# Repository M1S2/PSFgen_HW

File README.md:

# PS_Fgen_HW
Hardware for an PowerSupply and Functiongenerator build from an ATX power supply.

## ATX Supply
The hardware of the power supply and function generator is based on the following ATX supply:
``Yuan Kee 230P ATX``

By using another ATX supply, some output capabilities can be changed / enhanced.

## Input / Output Capabilities

The power supply and function generator features the following capabilites:

### Power Supply output (PS+)
One power supply output is available.
Connector		| PS+
-----------------------	| -----------------
Voltage			| 0 .. 10 V DC
Current			| 0 .. 2 A
Protections		| OVP, OCP, OPP

The voltage and current regulation is done in firmware.
The protections are implemented in firmware, too.

### DDS outputs (DDS1, DDS2)
Two direct digital synthesis outputs are available.
Connector		| DDS1						| DDS2
-----------------------	| ---------------------------------------------	| ---------------------------------------------
Amplitude		| 0 .. 20 Vpp					| 0 .. 20 Vpp
Offset			| -10 V .. 10 V					| -10 V .. 10 V
Frequency		| approx. max. 170 kHz				| approx. max. 170 kHz
Waveforms		| FW defined (Sine, Square, Triangle, ...)	| FW defined (Sine, Square, Triangle, ...)

The waveforms are defined in firmware. Default waveforms like sine, square and triangle are supported. By using DDS it is possible to even generate user defined waveforms.
The maximum frequency is limited by the low pass filter after the DAC outputs. The cutoff frequency is approximately 170 kHz. The real frequency range depends on the DDS implementation in the firmware!

### DMM inputs (DMM1, DMM2)
Two digital multimeter inputs are available.
Connector	| DMM1		| DMM2
---------------	| -------------	| ---------------
Input Range	| 0 .. 20 V DC	| 0 .. 20 V DC

Negative voltages on the DMM inputs between -20 V and 0 V are allowed but the output is clipped to 0 V!
The measured voltage for negative inputs is 0 V and a warning signal is generated.

### USB outputs
Two USB outputs are available. They are connected to the 5V output of the ATX supply. So the combined current capability for both USB ports are 23 A.

### USB input
The USB input can be used to communicate to the device via serial port.

### ATX outputs
All output voltages of the ATX supply are directly available through connectors on the connector panel. The currents are directly depending on the used ATX supply (values for the Yuan Kee 230P ATX).
Connector		| +5V	| +3V3	| +12V	| -12V
-----------------------	| -----	| -----	| -----	| -----
Voltage			| 5 V	| 3,3 V	| 12 V	| -12 V
Current (max.)		| 23 A	| 14 A	| 9 A	| 0.8 A

## User Interface

The user interface is made up of the following components:
- Graphical display: A 320x240 pixel graphical LCD is used to display the device status and current settings.
- Encoder: A rotary encoder can be used for value editing and menu navigation.
- KeyPad: A 16 button keypad can be used for value editing and menu navigation.
- OnOffControls: A PCB with buttons and LEDs for faster enabling of the channels and status display.

The user interface logic is defined by the firmware.

## Electronic
The electronic is divided into the following PCBs:
- **FrontPanel:** The front panel is containing 16 push buttons forming a 4x4 keypad and a rotary encoder for user input. It is connected to the MainBoard using a ribbon cable.
- **MainBoard:** The main board is containing all other components that can be grouped like following:
	- *Microcontroller*: The main controller of the power supply and function generator. It controls everything from user input handling to output generation. The used type is an ATmega1284P.
	- *Serial communication:* A FT232RL USB-UART IC is used for serial communication to the microcontroller via USB.
	- *GLCD:* The used graphic LCD model is ``ILI9341``. It has 320x240 pixels and is controllable via SPI. **Important:** The display uses a 3.3 V logic level!
	- *ATX voltage monitors:* The ATX 5 V and 3.3 V lines are each directly connected to ADCs of the microcontroller. The 12V and -12V lines aren't monitored anymore because the input pins were needed for other purposes.
	- *DMM inputs:* The two DMM inputs can be used to measure positive input voltages. The resistor divider scales the input voltage so that the maximum DMM input voltage equals 5 V (maximum allowed voltage of the microcontroller ADC inputs).  **Important:** Voltages higher than the maximum DMM input voltage can damage the inputs.
	- *DDS outputs:* The two DDS output signals are generated by a dual output DAC IC (MCP4921, output 0..5 V for each output) followed by an offset and amplification stage (used to create a range of -10 V .. 10 V). The output is buffered by an OpAmp and two transistors for higher currents.
	- *PS output:* The PS output signal is generated by a single output DAC IC (MCP4921, output 0..5 V) and buffered by an OpAmp and two transistors for higher currents. The voltage at the PS output is measured by a simple resistor voltage divider. The current at the PS output is measured by transforming it into a voltage proportional to the current.
- **DMMRectifier:** The DMMRectifier is used to protect the ADC DMM inputs from negative inputs on the DMM1 and DMM2 connectors. Negative voltages are clipped to 0 V and a warning signal is generated when the voltage on the inputs are negative.
- **OnOffControls:** The OnOffControls are buttons and LEDs for faster enabling of the channels and status display.

The FrontPanel, DMMRectifier and OnOffControls PCBs were designed to be manufactured with toner transfer method.

The MainBoard PCB was too complex for manual manufacturing and was therefore made by JLCPCB.

!!! :warning: Caution: The MainBoard was designed to a size of 100 x 100 mm to fit the maximum size of JLCPCB. Eagle changed the maximum board size to 100 x 80 mm in 2022. Therefore the board can't be modified anymore. But the schematics are up-to-date. !!! 

## Housing
All housing components are made for the above ATX supply and are not guaranteed to fit for any other ATX supply. Nevertheless all construction files are available in the Mechanical folder and can be adapted, if neccessary.
The parts were designed using Autodesk Fusion 360 (.f3d files) and are exported as .stl files.
The .stl files were used to 3D print all components.
All parts are needed once, except the `Standfuss.stl` (needed 4x).

## Firmware
The firmware for this power supply and function generator is developed in another repository:
[GitHub - M1S2/PS_Fgen_FW: Firmware for an Power Supply and Function Generator build from an ATX power supply](https://github.com/M1S2/PS_Fgen_FW)

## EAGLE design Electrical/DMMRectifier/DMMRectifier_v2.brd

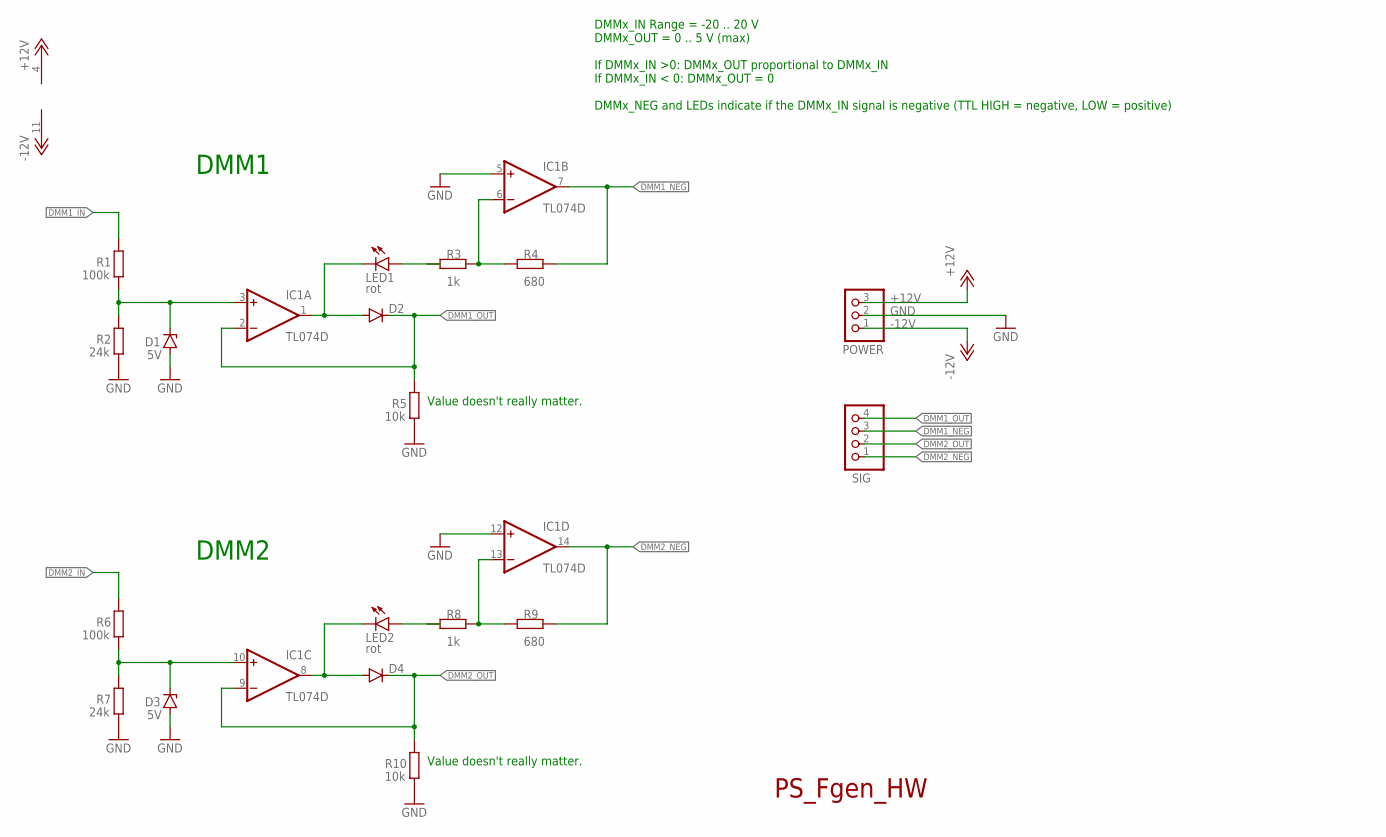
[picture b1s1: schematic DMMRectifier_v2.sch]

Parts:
D1, D3: 5V; SOD80C
D2, D4: DIODE-SOD80C; SOD80C
IC1: TL074D; SO14
LED1, LED2: rot; CHIPLED_0603
POWER: PINHD-1X3; 1X03
R1, R6: 100k; R0805
R2, R7: 24k; R0805
R3, R8: 1k; R0805
R4, R9: 680; R0805
R5, R10: 10k; R0805
SIG: PINHD-1X4; 1X04

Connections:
+12V: IC1.4 (V+), POWER.3
-12V: IC1.11 (V-), POWER.1
DMM1_IN: R1.2
DMM1_NEG: IC1.7 (OUT), R4.1, SIG.3
DMM1_OUT: D2.C, IC1.2 (-IN), R5.2, SIG.4
DMM2_IN: R6.2
DMM2_NEG: IC1.14 (OUT), R9.1, SIG.1
DMM2_OUT: D4.C, IC1.9 (-IN), R10.2, SIG.2
GND: D1.A, D3.A, IC1.5 (+IN), IC1.12 (+IN), POWER.2, R2.1, R5.1, R7.1, R10.1
unnamed: D1.C, IC1.3 (+IN), R1.1, R2.2
unnamed: D3.C, IC1.10 (+IN), R6.1, R7.2
unnamed: IC1.6 (-IN), R3.1, R4.2
unnamed: D2.A, IC1.1 (OUT), LED1.C
unnamed: LED1.A, R3.2
unnamed: IC1.13 (-IN), R8.1, R9.2
unnamed: D4.A, IC1.8 (OUT), LED2.C
unnamed: LED2.A, R8.2

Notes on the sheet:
PS_Fgen_HW
DMMx_IN Range = -20 .. 20 V DMMx_OUT = 0 .. 5 V (max) If DMMx_IN >0: DMMx_OUT proportional to DMMx_IN If DMMx_IN < 0: DMMx_OUT = 0 DMMx_NEG and LEDs indicate if the DMMx_IN signal is negative (TTL HIGH = negative, LOW = positive)
DMM1
DMM2
Value doesn't really matter.

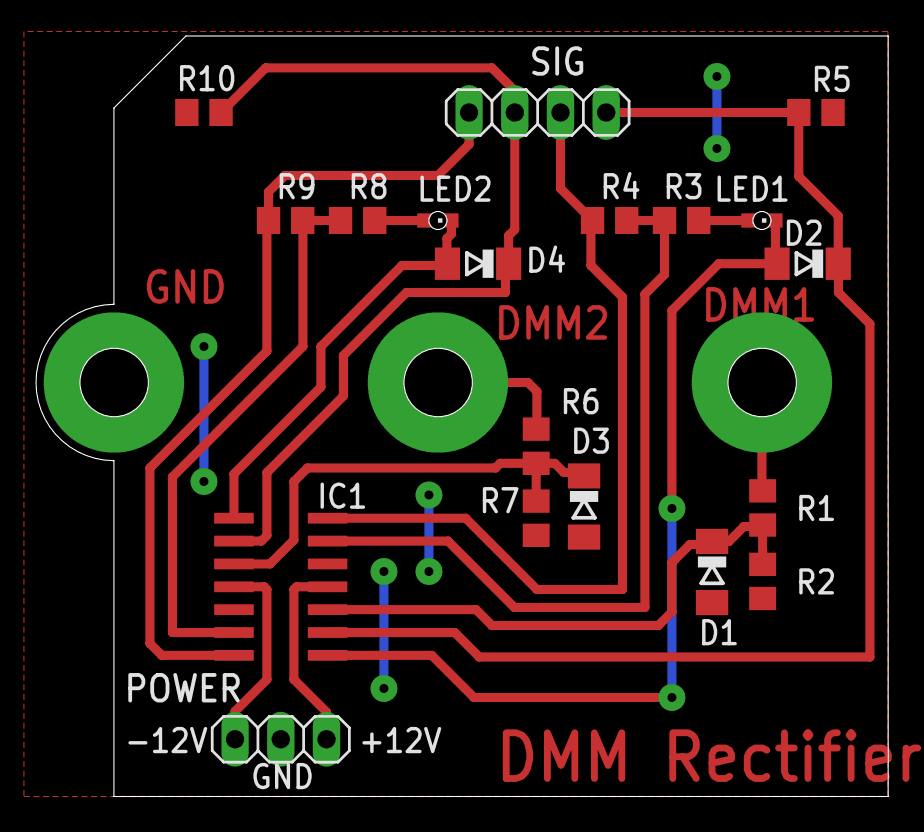
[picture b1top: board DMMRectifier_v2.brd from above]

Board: 2 copper layers, 47.3 x 42.2 mm, 19 parts (0 on the bottom side), 15 nets.

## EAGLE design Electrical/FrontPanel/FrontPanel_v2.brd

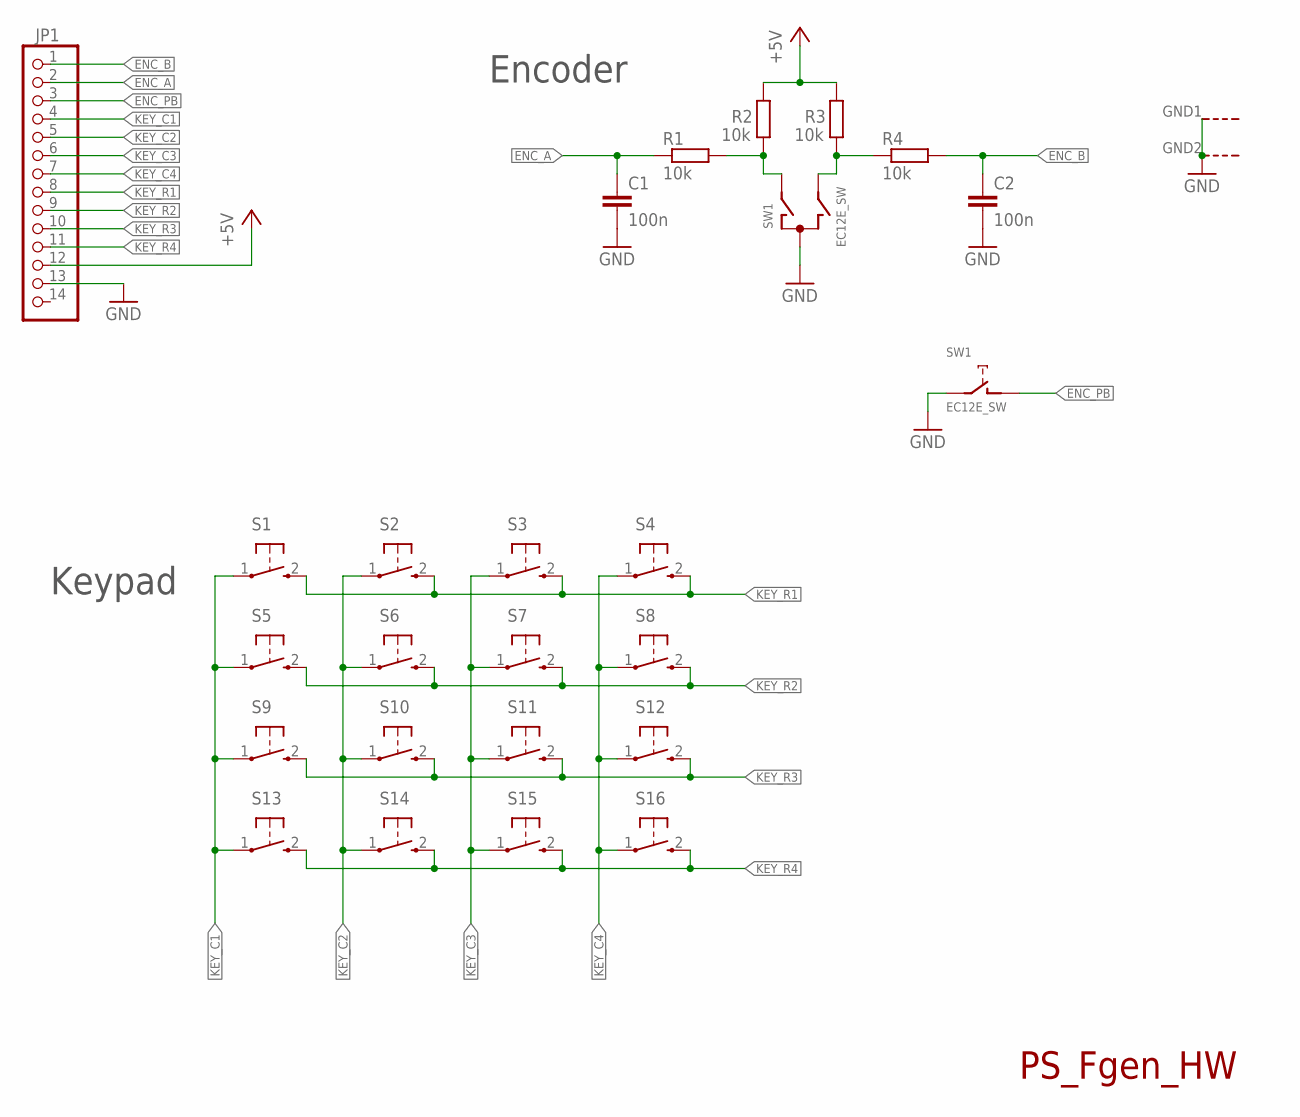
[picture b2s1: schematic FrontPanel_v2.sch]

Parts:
C1, C2: 100n; C0805
JP1: PINHD-1X14; 1X14
R1, R2, R3, R4: 10k; R0805
S1, S2, S3, S4, S5, S6, S7, S8, S9, S10, S11, S12, S13, S14, S15, S16: KURZHUBTASTER; B3F-10XX
SW1: EC12E_SW; ALPS_EC12E_SW

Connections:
+5V: JP1.12, R2.2, R3.2
ENC_A: C1.1, JP1.2, R1.1
ENC_B: C2.1, JP1.1, R4.2
ENC_PB: JP1.3, SW1.D (1)
GND: C1.2, C2.2, JP1.13, SW1.C, SW1.E (2), SW1.GND1 (G), SW1.GND2 (G)
KEY_C1: JP1.4, S1.1, S5.1, S9.1, S13.1
KEY_C2: JP1.5, S2.1, S6.1, S10.1, S14.1
KEY_C3: JP1.6, S3.1, S7.1, S11.1, S15.1
KEY_C4: JP1.7, S4.1, S8.1, S12.1, S16.1
KEY_R1: JP1.8, S1.2 (S), S2.2 (S), S3.2 (S), S4.2 (S)
KEY_R2: JP1.9, S5.2 (S), S6.2 (S), S7.2 (S), S8.2 (S)
KEY_R3: JP1.10, S9.2 (S), S10.2 (S), S11.2 (S), S12.2 (S)
KEY_R4: JP1.11, S13.2 (S), S14.2 (S), S15.2 (S), S16.2 (S)
unnamed: R1.2, R2.1, SW1.A
unnamed: R3.1, R4.1, SW1.B

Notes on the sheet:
PS_Fgen_HW
Keypad
Encoder

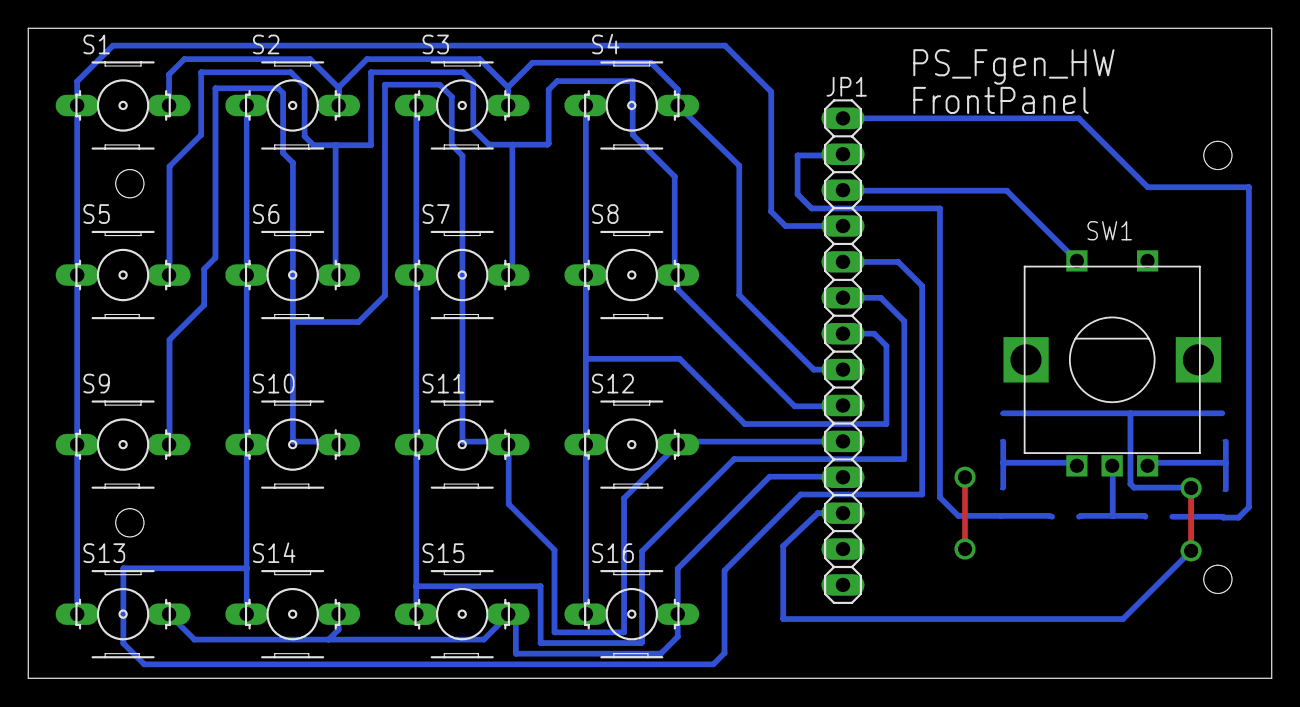
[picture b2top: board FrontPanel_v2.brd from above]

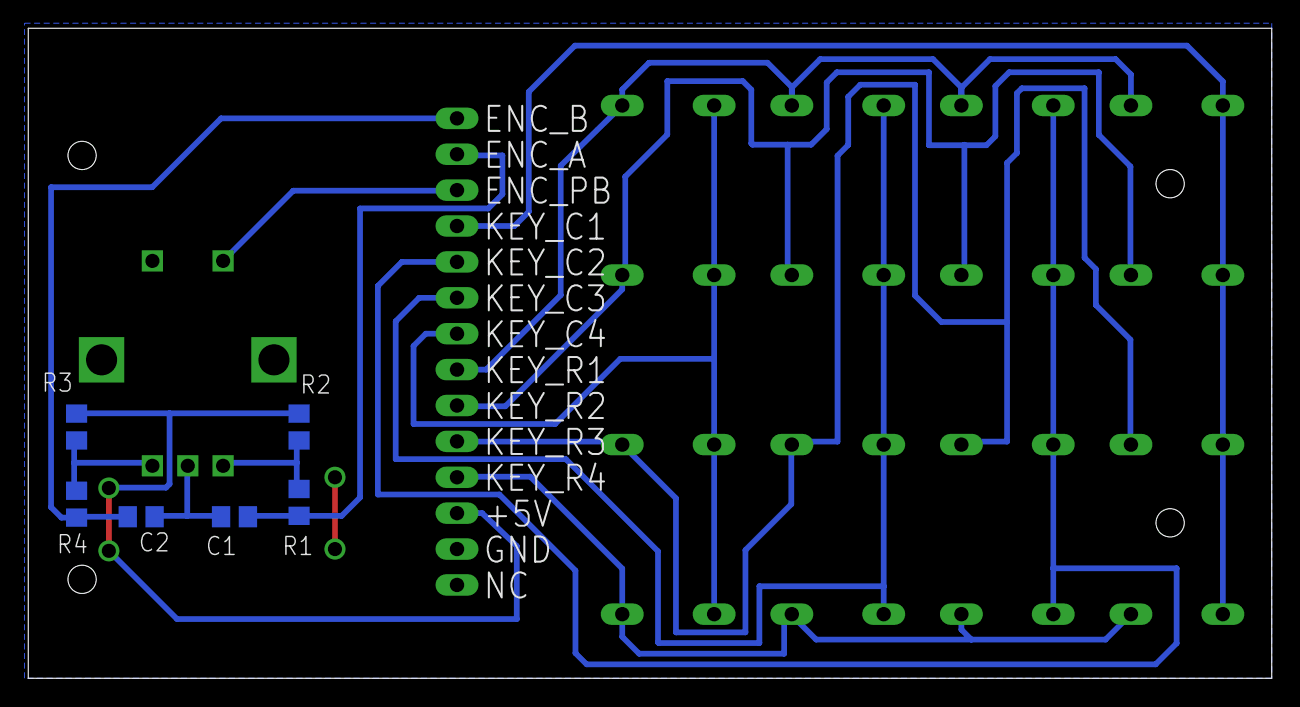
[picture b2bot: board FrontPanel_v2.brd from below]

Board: 2 copper layers, 88.0 x 46.0 mm, 24 parts (6 on the bottom side), 15 nets.

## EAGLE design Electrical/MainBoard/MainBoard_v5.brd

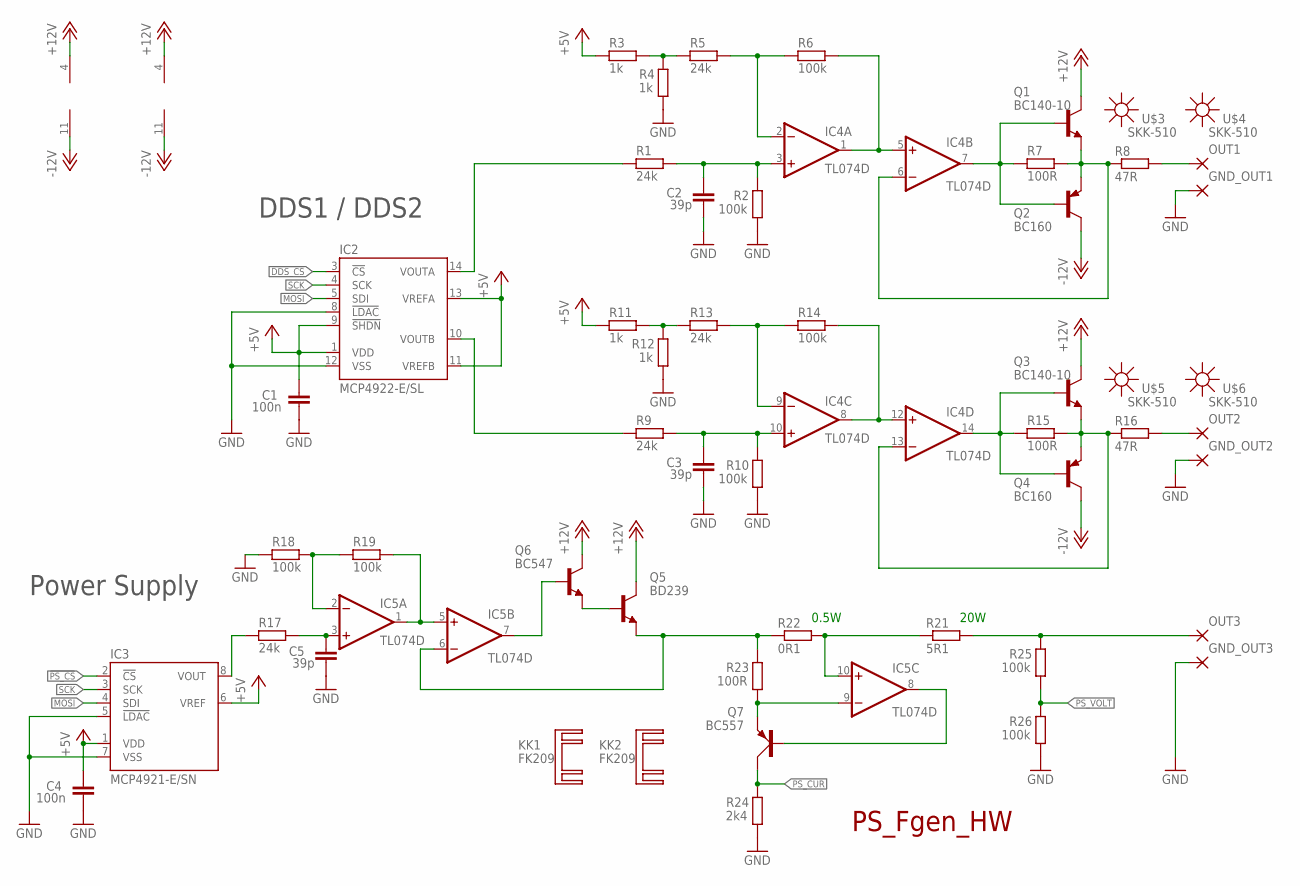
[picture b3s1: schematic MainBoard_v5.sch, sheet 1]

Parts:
C1, C4: 100n; C0805
C2, C3, C5: 39p; C0805
GND_OUT1, GND_OUT2, GND_OUT3: 2,54/1,0
IC2: MCP4922-E/SL; SO14
IC3: MCP4921-E/SN; SO08
IC4, IC5: TL074D; SO14
KK1, KK2: FK209
OUT1, OUT2, OUT3: 2,54/1,0
Q1, Q3: BC140-10; TO39
Q2, Q4: BC160; TO39
Q5: BD239; CB-274
Q6: BC547; TO92
Q7: BC557; SOT54A
R1, R5, R9, R13, R17: 24k; R0805
R2, R6, R10, R14, R18, R19, R25, R26: 100k; R0805
R3, R4, R11, R12: 1k; R0805
R7, R15, R23: 100R; R0805
R8, R16: 47R; 0411/15
R21: 5R1; 0411/15
R22: 0R1; 0411/15
R24: 2k4; R0805
U$3, U$4, U$5, U$6: SKK-510; SKK

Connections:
!DDS_CS: IC2.3 (!CS); also elsewhere on the board
!PS_CS: IC3.2 (!CS); also elsewhere on the board
+5V: C1.2, C4.2, IC2.1 (VDD), IC2.9 (!SHDN), IC2.11 (VREFB), IC2.13 (VREFA), IC3.1 (VDD), IC3.6 (VREF), R3.1, R11.1; also elsewhere on the board
+12V: IC4.4 (V+), IC5.4 (V+), Q1.3 (C), Q3.3 (C), Q5.T2 (C), Q6.3 (C); also elsewhere on the board
-12V: IC4.11 (V-), IC5.11 (V-), Q2.3 (C), Q4.3 (C); also elsewhere on the board
GND: C1.1, C2.1, C3.1, C4.1, C5.1, GND_OUT1.1, GND_OUT2.1, GND_OUT3.1, IC2.8 (!LDAC), IC2.12 (VSS), IC3.5 (!LDAC), IC3.7 (VSS), R2.1, R4.1, R10.1, R12.1, R18.1, R24.1, R26.1; also elsewhere on the board
MOSI: IC2.5 (SDI), IC3.4 (SDI); also elsewhere on the board
unnamed: IC2.14 (VOUTA), R1.1
unnamed: C2.2, IC4.3 (+IN), R1.2, R2.2
unnamed: R3.2, R4.2, R5.1
unnamed: IC4.2 (-IN), R5.2, R6.1
unnamed: IC4.7 (OUT), Q1.2 (B), Q2.2 (B), R7.1
unnamed: IC4.1 (OUT), IC4.5 (+IN), R6.2
unnamed: IC4.6 (-IN), Q1.1 (E), Q2.1 (E), R7.2, R8.1
unnamed: R11.2, R12.2, R13.1
unnamed: IC4.9 (-IN), R13.2, R14.1
unnamed: C3.2, IC4.10 (+IN), R9.2, R10.2
unnamed: IC4.8 (OUT), IC4.12 (+IN), R14.2
unnamed: IC2.10 (VOUTB), R9.1
unnamed: IC4.14 (OUT), Q3.2 (B), Q4.2 (B), R15.1
unnamed: IC4.13 (-IN), Q3.1 (E), Q4.1 (E), R15.2, R16.1
unnamed: IC3.8 (VOUT), R17.1
unnamed: C5.2, IC5.3 (+IN), R17.2
unnamed: IC5.2 (-IN), R18.2, R19.1
unnamed: IC5.6 (-IN), Q5.G (E), R22.1, R23.2
unnamed: IC5.1 (OUT), IC5.5 (+IN), R19.2
unnamed: Q5.T1 (B), Q6.1 (E)
unnamed: OUT3.1, R21.2, R25.2
unnamed: IC5.9 (-IN), Q7.E, R23.1
unnamed: IC5.8 (OUT), Q7.B
unnamed: OUT2.1, R16.2
unnamed: OUT1.1, R8.2
unnamed: IC5.7 (OUT), Q6.2 (B)
unnamed: IC5.10 (+IN), R21.1, R22.2
PS_CUR: Q7.C, R24.2; also elsewhere on the board
PS_VOLT: R25.1, R26.2; also elsewhere on the board
SCK: IC2.4 (SCK), IC3.3 (SCK); also elsewhere on the board

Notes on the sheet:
PS_Fgen_HW
DDS1 / DDS2
Power Supply
0.5W
20W

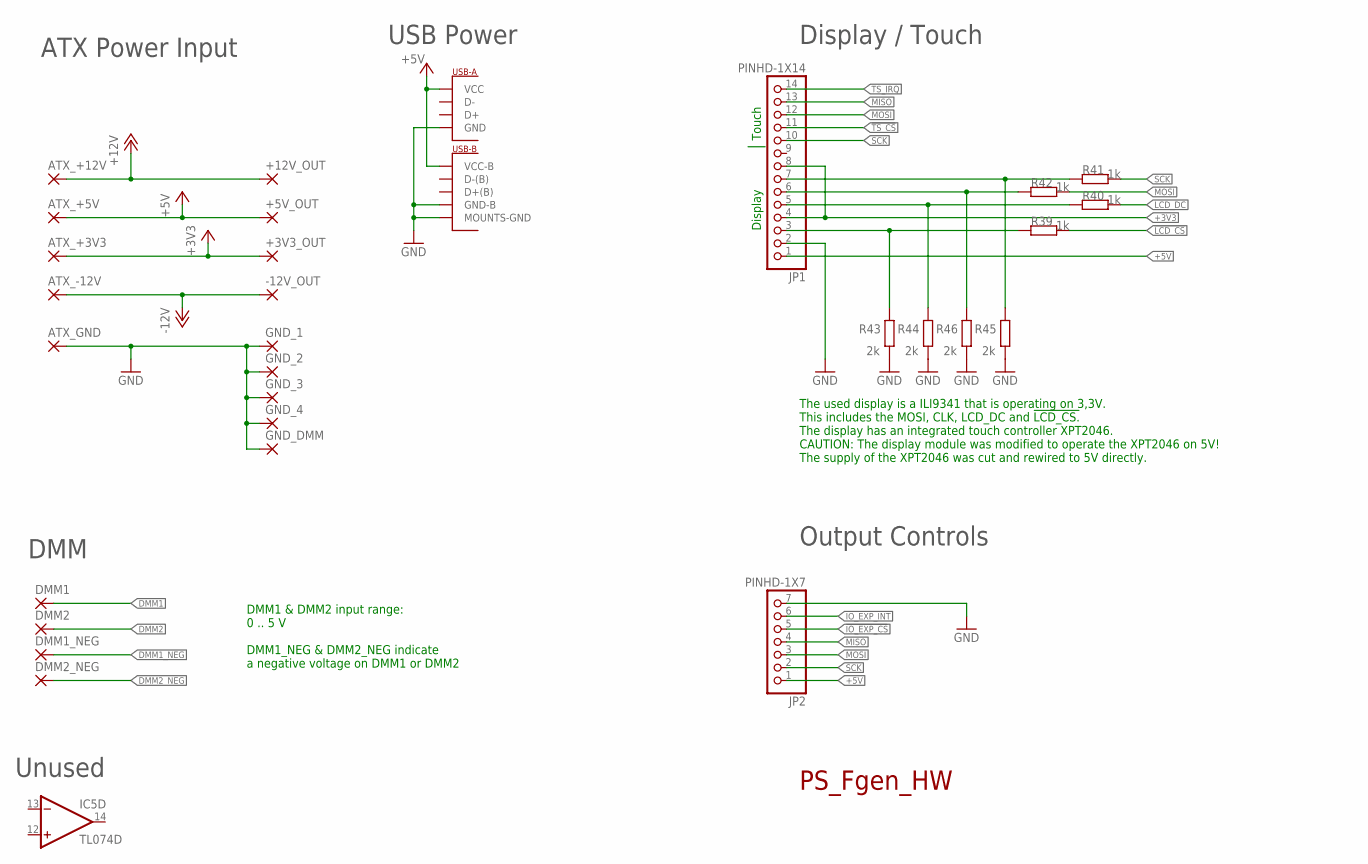
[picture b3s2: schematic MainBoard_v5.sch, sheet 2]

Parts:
+3V3_OUT, +5V_OUT, +12V_OUT: 2,54/1,0
-12V_OUT: 2,54/1,0
ATX_+3V3, ATX_+5V, ATX_+12V: 2,54/1,0
ATX_-12V: 2,54/1,0
ATX_GND: 2,54/1,0
DMM1, DMM1_NEG, DMM2, DMM2_NEG: 2,54/1,0
GND_1, GND_2, GND_3, GND_4: 2,54/1,0
GND_DMM: 2,54/1,0
IC5: TL074D; SO14
JP1: PINHD-1X14; 1X14
JP2: PINHD-1X7; 1X07
R39, R40, R41, R42: 1k; R0805
R43, R44, R45, R46: 2k; R0805
U$2: DUAL-PORT-USB-REC; DUAL-PORT-USB

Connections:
!IO_EXP_CS: JP2.5; also elsewhere on the board
!LCD_CS: R39.2; also elsewhere on the board
!LCD_CS_3V3: JP1.3, R39.1, R43.1
!TS_CS: JP1.11; also elsewhere on the board
+3V3: +3V3_OUT.1, ATX_+3V3.1, JP1.4, JP1.8; also elsewhere on the board
+5V: +5V_OUT.1, ATX_+5V.1, JP1.1, JP2.1, U$2.P$10 (VCC-B), U$2.P$12 (VCC); also elsewhere on the board
+12V: +12V_OUT.1, ATX_+12V.1; also elsewhere on the board
-12V: -12V_OUT.1, ATX_-12V.1; also elsewhere on the board
DMM1: DMM1.1; also elsewhere on the board
DMM1_NEG: DMM1_NEG.1; also elsewhere on the board
DMM2: DMM2.1; also elsewhere on the board
DMM2_NEG: DMM2_NEG.1; also elsewhere on the board
GND: ATX_GND.1, GND_1.1, GND_2.1, GND_3.1, GND_4.1, GND_DMM.1, JP1.2, JP2.7, R43.2, R44.2, R45.2, R46.2, U$2.GND (MOUNTS-GND), U$2.P$2 (MOUNTS-GND), U$2.P$3 (MOUNTS-GND), U$2.P$4 (MOUNTS-GND), U$2.P$9 (GND-B), U$2.P$11 (GND); also elsewhere on the board
IO_EXP_INT: JP2.6; also elsewhere on the board
LCD_DC: R40.2; also elsewhere on the board
MISO: JP1.13, JP2.4; also elsewhere on the board
MOSI: JP1.12, JP2.3, R42.2; also elsewhere on the board
MOSI_3V3: JP1.6, R42.1, R46.1
unnamed: JP1.5, R40.1, R44.1
SCK: JP1.10, JP2.2, R41.2; also elsewhere on the board
SCK_3V3: JP1.7, R41.1, R45.1
TS_IRQ: JP1.14; also elsewhere on the board

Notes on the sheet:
PS_Fgen_HW
Display / Touch
Unused
DMM
USB Power
ATX Power Input
DMM1 & DMM2 input range: 0 .. 5 V DMM1_NEG & DMM2_NEG indicate a negative voltage on DMM1 or DMM2
The used display is a ILI9341 that is operating on 3,3V. This includes the MOSI, CLK, LCD_DC and !LCD_CS. The display has an integrated touch controller XPT2046. CAUTION: The display module was modified to operate the XPT2046 on 5V! The supply of the XPT2046 was cut and rewired to 5V directly.
Display
Touch
Output Controls

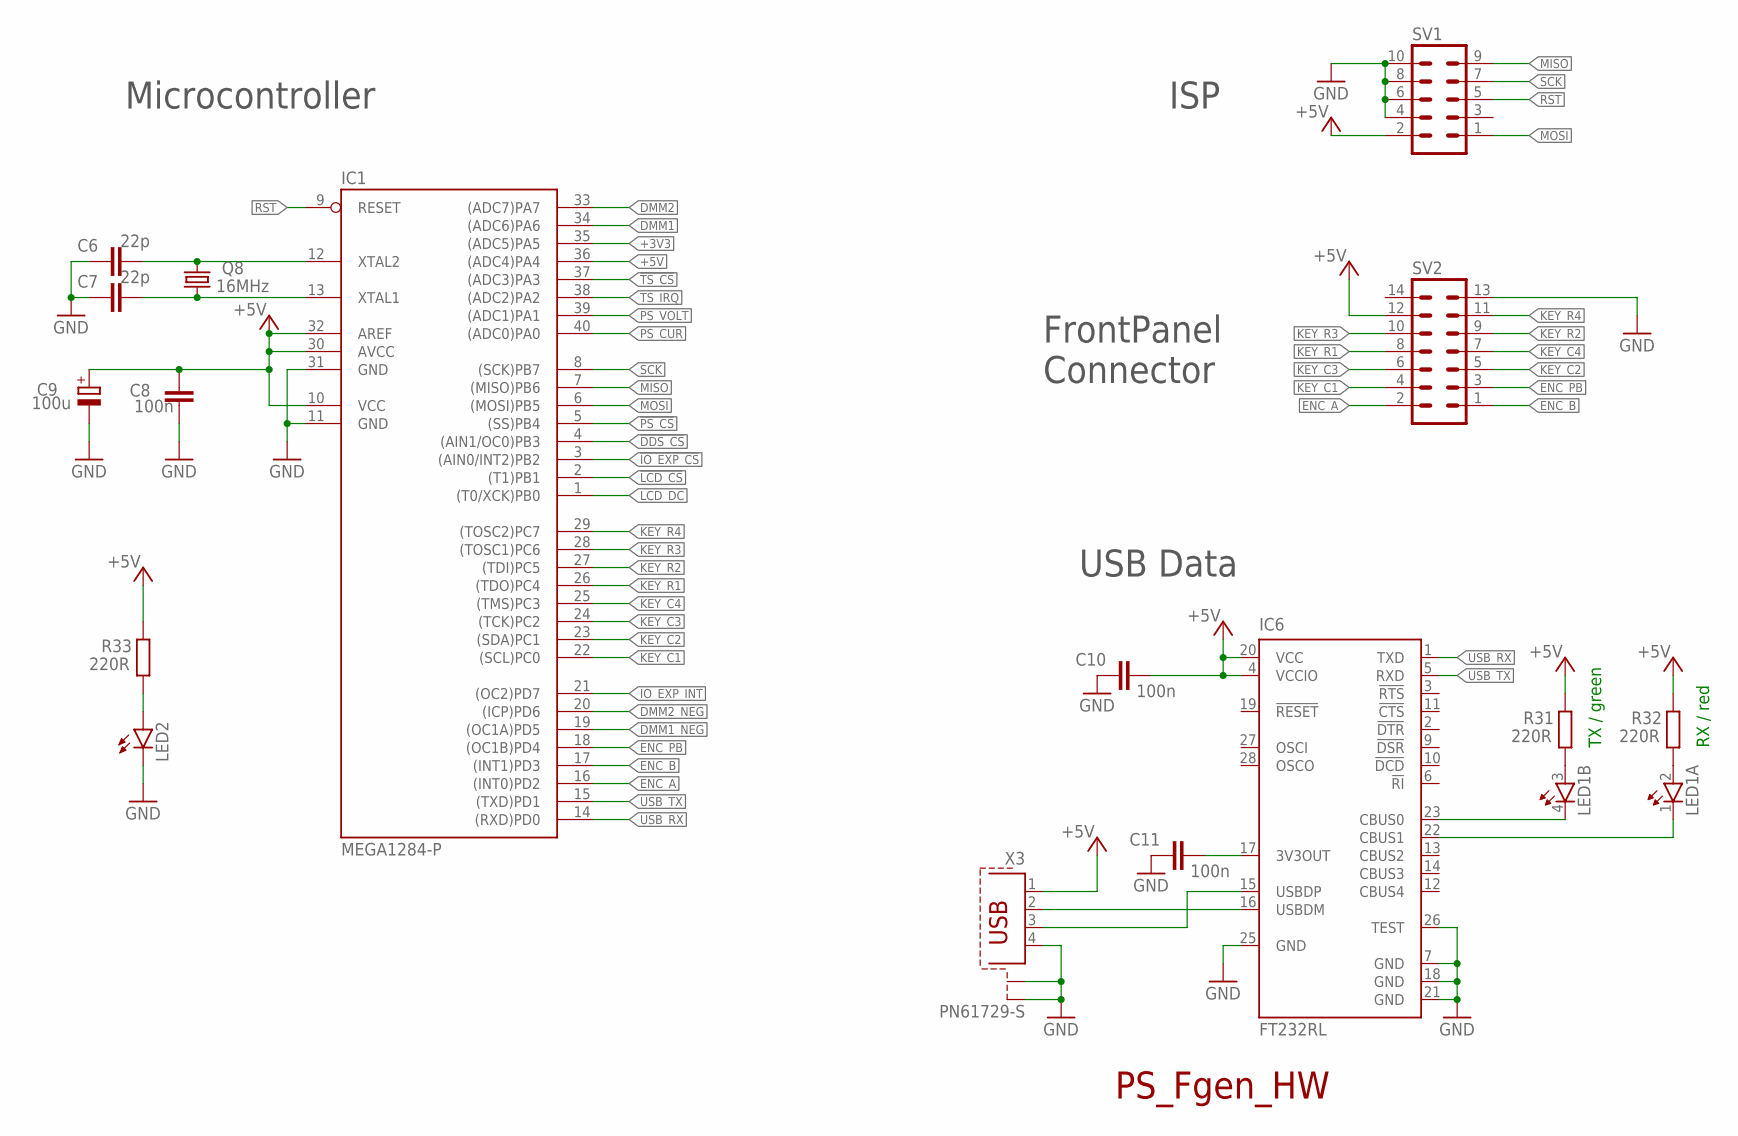
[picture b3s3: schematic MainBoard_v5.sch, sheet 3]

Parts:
C6, C7: 22p; C0805
C8, C10, C11: 100n; C0805
C9: 100u; PANASONIC_D
IC1: MEGA1284-P; DIL40
IC6: FT232RL; SSOP28
LED1: TOPLED-2--; P-LCC-4-2
LED2: LEDCHIP-LED0805; CHIP-LED0805
Q8: 16MHz; HC49/S
R31, R32, R33: 220R; R0805
SV1: ML10
SV2: ML14
X3: PN61729-S

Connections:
!DDS_CS: IC1.4 ((AIN1/OC0)PB3); also elsewhere on the board
!IO_EXP_CS: IC1.3 ((AIN0/INT2)PB2); also elsewhere on the board
!LCD_CS: IC1.2 ((T1)PB1); also elsewhere on the board
!PS_CS: IC1.5 ((SS)PB4); also elsewhere on the board
!TS_CS: IC1.37 ((ADC3)PA3); also elsewhere on the board
+3V3: IC1.35 ((ADC5)PA5); also elsewhere on the board
+5V: C8.2, C9.+, C10.1, IC1.10 (VCC), IC1.30 (AVCC), IC1.32 (AREF), IC1.36 ((ADC4)PA4), IC6.4 (VCCIO), IC6.20 (VCC), R31.2, R32.2, R33.2, SV1.2, SV2.12, X3.1; also elsewhere on the board
DMM1: IC1.34 ((ADC6)PA6); also elsewhere on the board
DMM1_NEG: IC1.19 ((OC1A)PD5); also elsewhere on the board
DMM2: IC1.33 ((ADC7)PA7); also elsewhere on the board
DMM2_NEG: IC1.20 ((ICP)PD6); also elsewhere on the board
ENC_A: IC1.16 ((INT0)PD2), SV2.2
ENC_B: IC1.17 ((INT1)PD3), SV2.1
ENC_PB: IC1.18 ((OC1B)PD4), SV2.3
GND: C6.2, C7.2, C8.1, C9.-, C10.2, C11.2, IC1.11 (GND), IC1.31 (GND), IC6.7 (GND), IC6.18 (GND), IC6.21 (GND), IC6.25 (GND), IC6.26 (TEST), LED2.C, SV1.4, SV1.6, SV1.8, SV1.10, SV2.13, X3.4, X3.S1, X3.S2; also elsewhere on the board
IO_EXP_INT: IC1.21 ((OC2)PD7); also elsewhere on the board
KEY_C1: IC1.22 ((SCL)PC0), SV2.4
KEY_C2: IC1.23 ((SDA)PC1), SV2.5
KEY_C3: IC1.24 ((TCK)PC2), SV2.6
KEY_C4: IC1.25 ((TMS)PC3), SV2.7
KEY_R1: IC1.26 ((TDO)PC4), SV2.8
KEY_R2: IC1.27 ((TDI)PC5), SV2.9
KEY_R3: IC1.28 ((TOSC1)PC6), SV2.10
KEY_R4: IC1.29 ((TOSC2)PC7), SV2.11
LCD_DC: IC1.1 ((T0/XCK)PB0); also elsewhere on the board
MISO: IC1.7 ((MISO)PB6), SV1.9; also elsewhere on the board
MOSI: IC1.6 ((MOSI)PB5), SV1.1; also elsewhere on the board
unnamed: C7.1, IC1.13 (XTAL1), Q8.1
unnamed: C6.1, IC1.12 (XTAL2), Q8.2
unnamed: C11.1, IC6.17 (3V3OUT)
unnamed: IC6.16 (USBDM), X3.2
unnamed: IC6.15 (USBDP), X3.3
unnamed: IC6.23 (CBUS0), LED1.4 (C)
unnamed: IC6.22 (CBUS1), LED1.1 (C)
unnamed: LED1.3 (A), R31.1
unnamed: LED1.2 (A), R32.1
unnamed: LED2.A, R33.1
PS_CUR: IC1.40 ((ADC0)PA0); also elsewhere on the board
PS_VOLT: IC1.39 ((ADC1)PA1); also elsewhere on the board
RST: IC1.9 (RESET), SV1.5
SCK: IC1.8 ((SCK)PB7), SV1.7; also elsewhere on the board
TS_IRQ: IC1.38 ((ADC2)PA2); also elsewhere on the board
USB_RX: IC1.14 ((RXD)PD0), IC6.1 (TXD)
USB_TX: IC1.15 ((TXD)PD1), IC6.5 (RXD)

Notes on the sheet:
TX / green
RX / red
PS_Fgen_HW
Microcontroller
ISP
FrontPanel Connector
USB Data

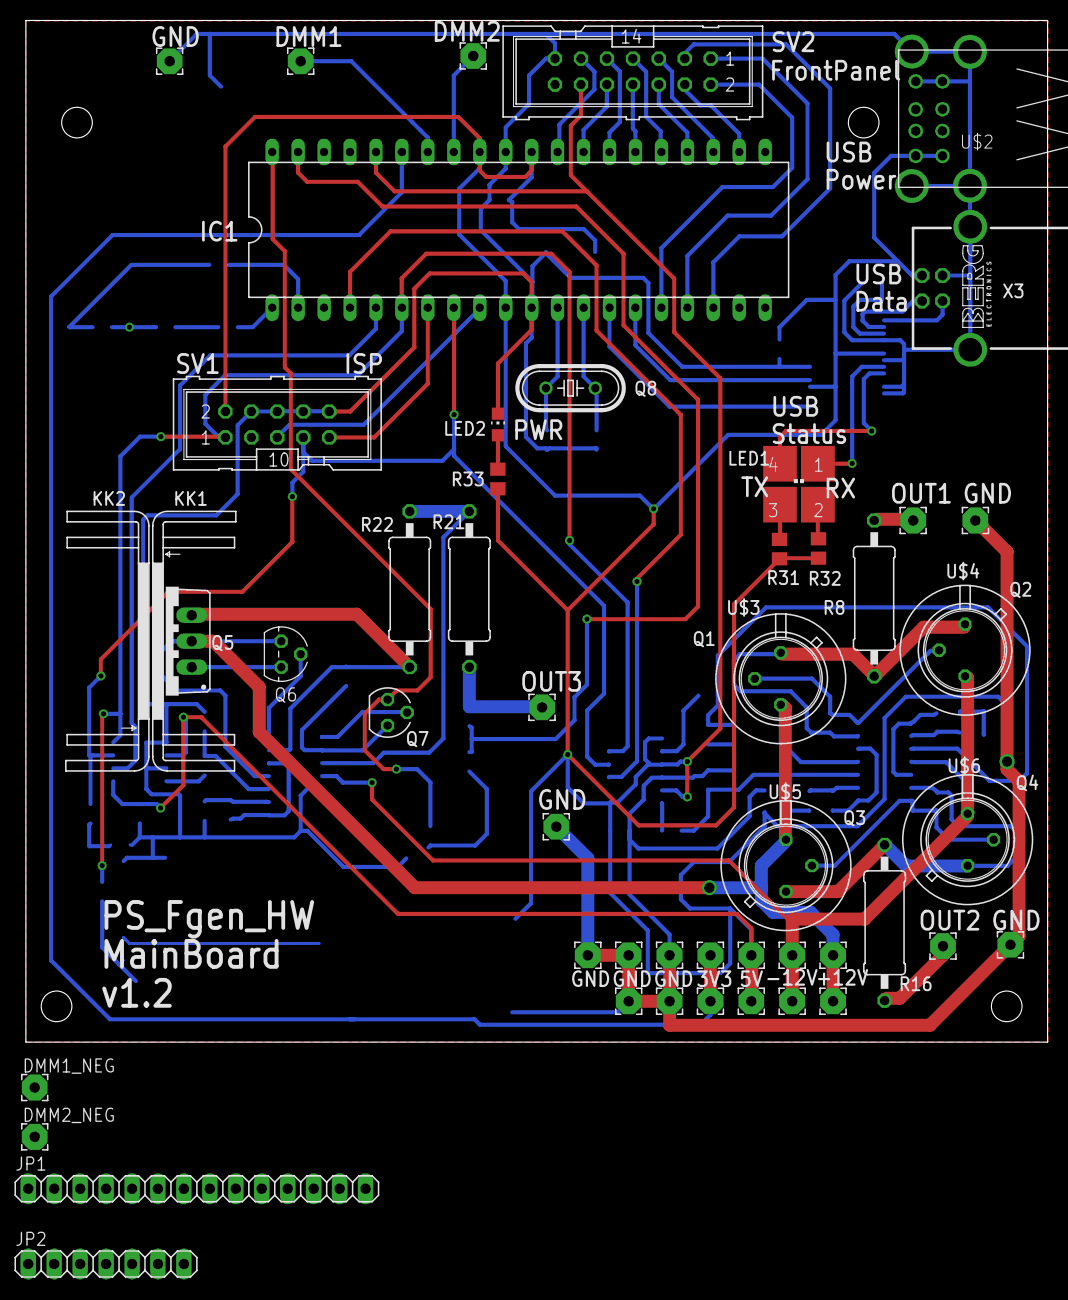
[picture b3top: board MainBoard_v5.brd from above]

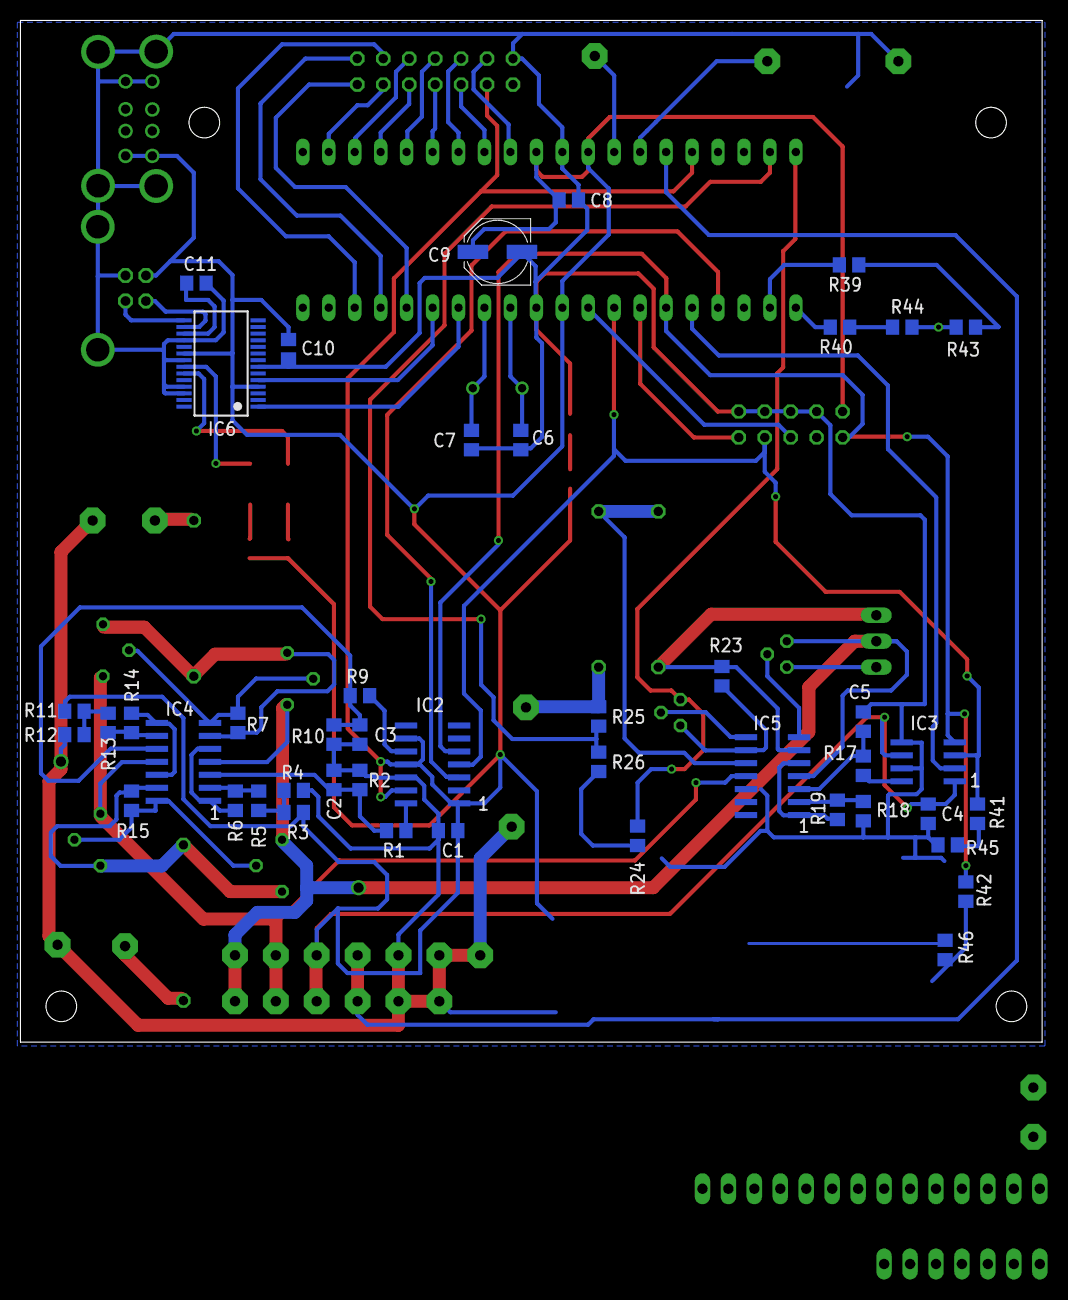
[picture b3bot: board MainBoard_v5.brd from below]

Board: 2 copper layers, 100.0 x 100.0 mm, 99 parts (45 on the bottom side), 77 nets.

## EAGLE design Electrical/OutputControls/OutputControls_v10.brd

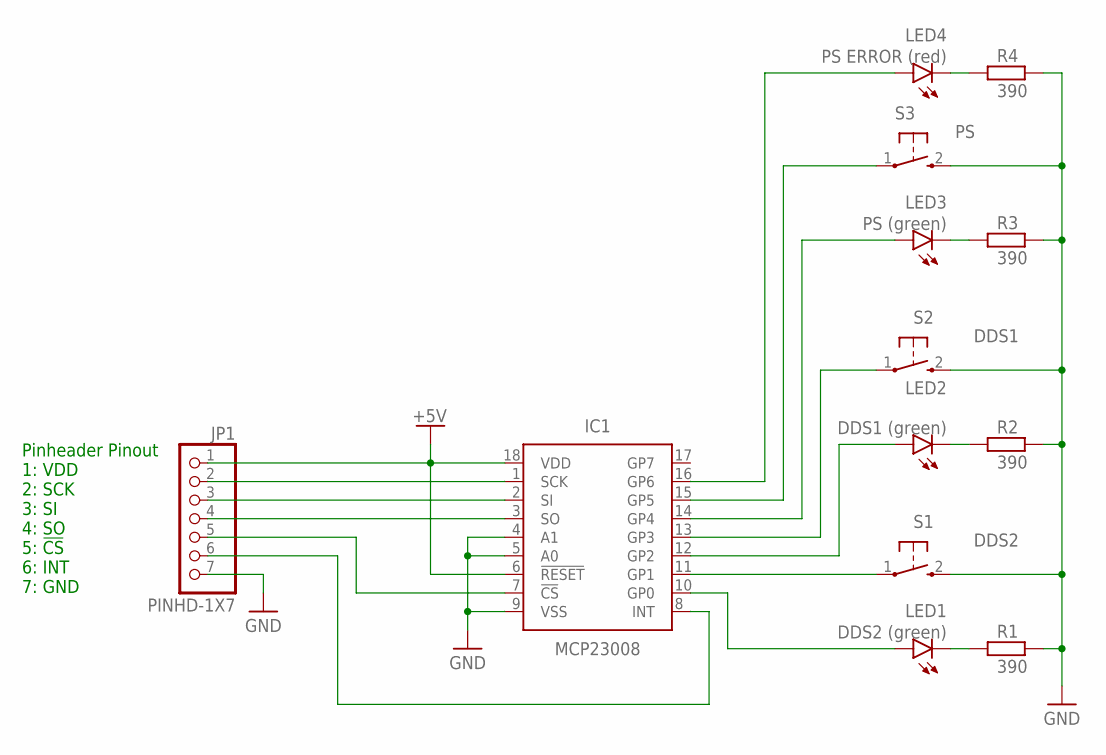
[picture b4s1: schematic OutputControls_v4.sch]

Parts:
IC1: MCP23008; SOIC127P1030X265-18N
JP1: PINHD-1X7; 1X07
LED1: DDS2 (green); CHIPLED_0603
LED2: DDS1 (green); CHIPLED_0603
LED3: PS (green); CHIPLED_0603
LED4: PS ERROR (red); CHIPLED_0603
R1, R2, R3, R4: 390; R0805
S1: DDS2; B3F-10XX
S2: DDS1; B3F-10XX
S3: PS; B3F-10XX

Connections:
+5V: IC1.6 (!RESET), IC1.18 (VDD), JP1.1
GND: IC1.4 (A1), IC1.5 (A0), IC1.9 (VSS), JP1.7, R1.2, R2.2, R3.2, R4.2, S1.2 (S), S2.2 (S), S3.2 (S)
unnamed: IC1.10 (GP0), LED1.A
unnamed: IC1.11 (GP1), S1.1
unnamed: IC1.12 (GP2), LED2.A
unnamed: LED1.C, R1.1
unnamed: LED2.C, R2.1
unnamed: LED3.C, R3.1
unnamed: IC1.13 (GP3), S2.1
unnamed: IC1.14 (GP4), LED3.A
unnamed: IC1.15 (GP5), S3.1
unnamed: LED4.C, R4.1
unnamed: IC1.1 (SCK), JP1.2
unnamed: IC1.2 (SI), JP1.3
unnamed: IC1.3 (SO), JP1.4
unnamed: IC1.7 (!CS), JP1.5
unnamed: IC1.8 (INT), JP1.6
unnamed: IC1.16 (GP6), LED4.A

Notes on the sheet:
Pinheader Pinout 1: VDD 2: SCK 3: SI 4: SO 5: !CS 6: INT 7: GND

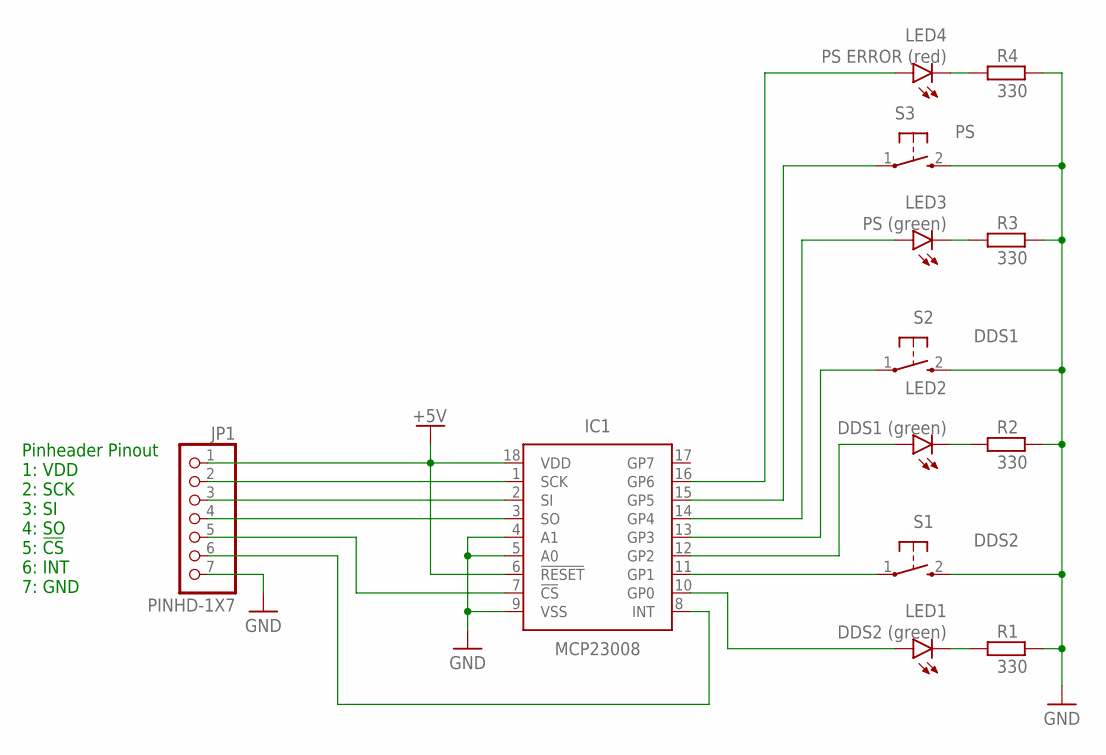
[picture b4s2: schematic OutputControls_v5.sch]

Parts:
IC1: MCP23008; SOIC127P1030X265-18N
JP1: PINHD-1X7; 1X07
LED1: DDS2 (green); CHIPLED_0603
LED2: DDS1 (green); CHIPLED_0603
LED3: PS (green); CHIPLED_0603
LED4: PS ERROR (red); CHIPLED_0603
R1, R2, R3, R4: 330; R0805
S1: DDS2; B3F-10XX
S2: DDS1; B3F-10XX
S3: PS; B3F-10XX

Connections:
+5V: IC1.6 (!RESET), IC1.18 (VDD), JP1.1
GND: IC1.4 (A1), IC1.5 (A0), IC1.9 (VSS), JP1.7, R1.2, R2.2, R3.2, R4.2, S1.2 (S), S2.2 (S), S3.2 (S)
unnamed: IC1.10 (GP0), LED1.A
unnamed: IC1.11 (GP1), S1.1
unnamed: IC1.12 (GP2), LED2.A
unnamed: LED1.C, R1.1
unnamed: LED2.C, R2.1
unnamed: LED3.C, R3.1
unnamed: IC1.13 (GP3), S2.1
unnamed: IC1.14 (GP4), LED3.A
unnamed: IC1.15 (GP5), S3.1
unnamed: LED4.C, R4.1
unnamed: IC1.1 (SCK), JP1.2
unnamed: IC1.2 (SI), JP1.3
unnamed: IC1.3 (SO), JP1.4
unnamed: IC1.7 (!CS), JP1.5
unnamed: IC1.8 (INT), JP1.6
unnamed: IC1.16 (GP6), LED4.A

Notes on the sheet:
Pinheader Pinout 1: VDD 2: SCK 3: SI 4: SO 5: !CS 6: INT 7: GND
